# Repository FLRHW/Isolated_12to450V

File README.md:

<p align="center" width="100%">
  
</p>

***

<p align="center">
  
&nbsp; &nbsp; &nbsp; &nbsp;
  
</p>

***

# **Isolated step-up module**
This repository contains KiCad schematic and PCB layout of a step-up module prototype, isolated, capable of producing outputs in the range of 160 V to 450 V from a 12 V supply.

## Project overview
This project documents the conversion of a commercial non-isolated step-up module originally purchased from AliExpress into isolated.

## Origin and scope
Original hardware: generic module purchased from AliExpress (exact vendor and listing may change over time, the following terms can help finding similar modules: "70W DC-DC 12V 24V To 200V-450V Voltage Adjustable Boost Power Converter Nixie Clock Tube Amplifier Capacitor Charging").  

Redesigned hardware: new schematic and PCB layout, but several parts from the original module have been reused (controller, transformer, connector, fuse and its holder, power MOSFET, output diode, trim-pot, power resistors and electrolytic capacitors). 

Status: prototype, partially tested. Not affiliated with, endorsed by, or supported by the original manufacturer or seller.

Contents: KiCad design files and supporting documentation.

## Intended use
This repository is intended for:
* Educational use and study of the circuit
* Repair, modification, or replacement of compatible hardware
* Integration into hobby or research projects, subject to any third‑party IP that may apply in your jurisdiction. Users are responsible for checking any patent, copyright, or regulatory constraints that may apply to their own use

## License
The KiCad design files and documentation in this repository are released under the CERN Open Hardware Licence v2 – Permissive (CERN‑OHL‑P‑2.0). SPDX identifier: CERN-OHL-P-2.0 See the LICENSE file for the full legal text and conditions.  

In short and non‑legal terms, you are free to use, modify, manufacture, and distribute hardware based on these files, provided you respect attribution requirements and the terms in the license.

## Trademarks and third‑party rights
All product names, logos, and brands of the original module are the property of their respective owners and are not included or licensed here.  

Any reference to third‑party marks is purely descriptive and does not imply endorsement or affiliation.  

If you are the rights holder for the original hardware and have concerns about this documentation, please open an issue in the repository.

## Safety and disclaimer
* The author takes no responsibility for any injury, death or damage arising from the use, direct or indirect, of the design or otherwise any information from this repository
* You shall not build this or any prototype based on this design unless you are absolutely sure of your abilities dealing with this type of circuit
* High voltage can cause injury, death, or damage to equipment. Ensure appropriate protections and testing procedures are followed
* Use it at your own risk. Always review the schematic, layout, and component ratings before using it
* The design is provided as is, with no warranty of any kind

## Contributing
Contributions are welcome.

***

## DIRECTORY STRUCTURE
    │
    ├─ Computations       # Misc calculations
    ├─ HTML               # HTML files for generated webpage
    ├─ Images             # Pictures and renders
    │
    ├─ kibot_resources    # External resources for KiBot
    │  ├─ colors          # Color theme for KiCad
    │  ├─ fonts           # Fonts used in the project
    │  ├─ scripts         # External scripts used with KiBot
    │  └─ templates       # Templates for KiBot generated reports
    │
    ├─ kibot_yaml         # KiBot YAML config files
    ├─ KiRI               # KiRI (PCB diff viewer) files
    │
    ├─ lib                # KiCad footprint and symbol libraries
    │  ├─ 3d_models       # Component 3D models
    │  ├─ lib_fp          # Footprint libraries
    │  └─ lib_sym         # Symbol libraries
    │
    ├─ Logos              # Logos
    │
    ├─ Manufacturing      # Assembly and fabrication documents
    │  ├─ Assembly        # Assembly documents (BoM, pos, notes)
    │  │
    │  └─ Fabrication     # Fabrication documents (ZIP, notes)
    │     ├─ Drill Tables # CSV drill tables
    │     └─ Gerbers      # Gerbers
    │
    ├─ Reports            # Reports for ERC/DRC
    ├─ Schematic          # PDF of schematic
    ├─ Templates          # Title block templates
    └─ Testing
       └─ Testpoints      # Testpoints tables

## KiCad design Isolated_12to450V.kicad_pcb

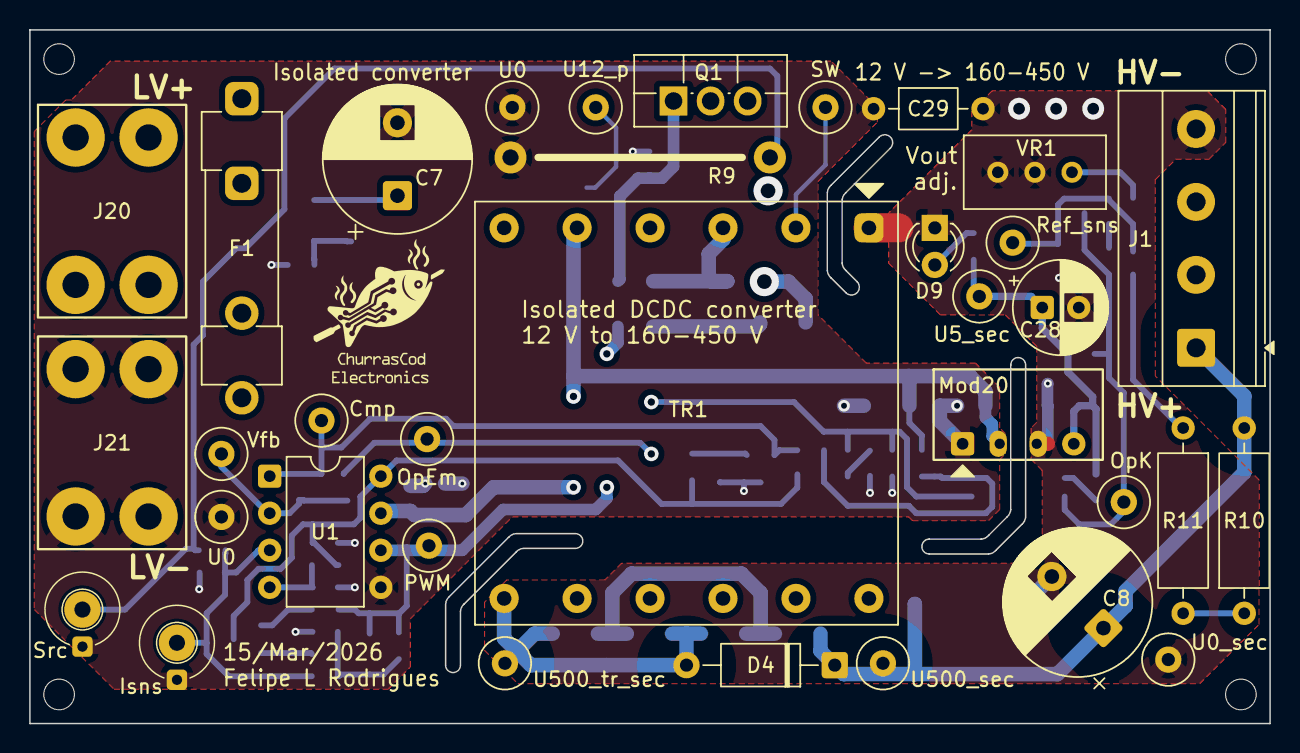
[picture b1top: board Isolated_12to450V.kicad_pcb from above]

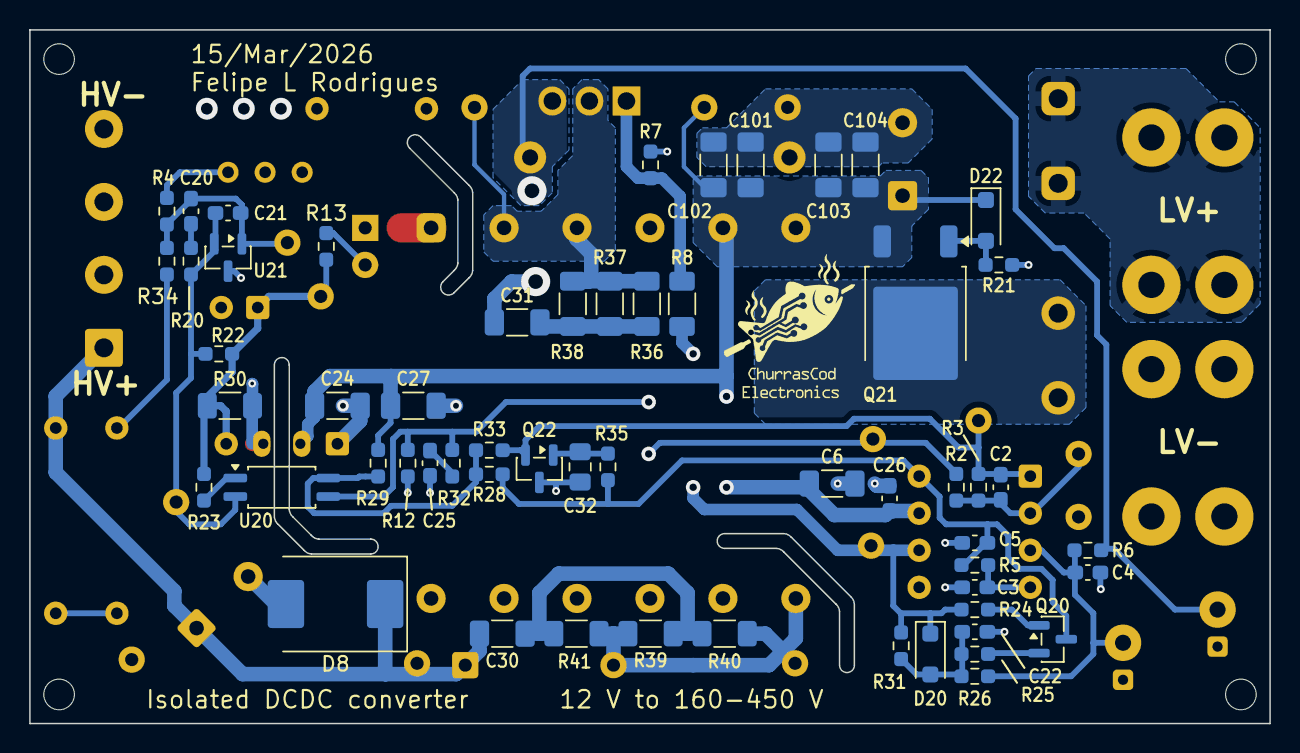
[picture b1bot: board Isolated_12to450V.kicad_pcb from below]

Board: 4 copper layers, 85.0 x 47.5 mm, 95 parts (57 on the bottom side), 35 nets.

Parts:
C2, C3, C4, C25: 1n; C_0603_1608Metric_Pad1.08x0.95mm_HandSolder
C5, C20, C26: 100n; C_0603_1608Metric_Pad1.08x0.95mm_HandSolder
C6, C24, C27, C101, C102, C103, C104: 4.7u; C_1206_3216Metric_Pad1.33x1.80mm_HandSolder
C7: 1000u; CP_Radial_D10.0mm_P5.00mm
C8: 10u; CP_Radial_D10.0mm_P5.00mm
C21: 100p; C_0603_1608Metric_Pad1.08x0.95mm_HandSolder
C22: 10n; C_0603_1608Metric_Pad1.08x0.95mm_HandSolder
C28: 100u; CP_Radial_D6.3mm_P2.50mm
C29: 1.5n; C_Axial_L3.8mm_D2.6mm_P7.50mm_Horizontal
C30: 220p; C_1206_3216Metric_Pad1.33x1.80mm_HandSolder
C31: 2.7n; C_1206_3216Metric_Pad1.33x1.80mm_HandSolder
C32: 1u; C_0805_2012Metric_Pad1.18x1.45mm_HandSolder
D4: UF4007; D_A-405_P10.16mm_Horizontal
D8: S15M; D_SMC
D9: LED; LED_D3.0mm
D20: PMEG4010CEH; D_SOD-123F
D22: BZT52B15; D_SOD-123F
F1: 10A; Fuse_5x20mm_w_holders
H1, H2, H3, H4: MountingHole; MountingHole_2.1mm
J1: Screw_Terminal_01x04; TerminalBlock_Phoenix_MKDS-1,5-4_1x04_P5.00mm_Horizontal
J20, J21: T44007
Mod20: WB2405S-1W; WB___S-1W
Q1: HY1707; TO-220F-3_Vertical
Q20: BC817; SOT-23
Q21: SUD50P06-15; TO-252-2
Q22: BC857; SOT-23
R2, R3, R21: 10k; R_0603_1608Metric_Pad0.98x0.95mm_HandSolder
R4: 2k7; R_0603_1608Metric_Pad0.98x0.95mm_HandSolder
R5: 15k; R_0603_1608Metric_Pad0.98x0.95mm_HandSolder
R6, R13, R29: 1k; R_0603_1608Metric_Pad0.98x0.95mm_HandSolder
R7: 5k1; R_0603_1608Metric_Pad0.98x0.95mm_HandSolder
R8: 20; R_1206_3216Metric_Pad1.30x1.75mm_HandSolder
R9: 13.7m; Shunt_alixp_module
R10, R11: 240k; R_Axial_DIN0309_L9.0mm_D3.2mm_P12.70mm_Horizontal
R12: 1k2; R_0603_1608Metric_Pad0.98x0.95mm_HandSolder
R20, R35: 100k; R_0603_1608Metric_Pad0.98x0.95mm_HandSolder
R22, R25, R31: 2k2; R_0603_1608Metric_Pad0.98x0.95mm_HandSolder
R23: 470; R_0603_1608Metric_Pad0.98x0.95mm_HandSolder
R24: 4k7; R_0603_1608Metric_Pad0.98x0.95mm_HandSolder
R26: 4.7k; R_0603_1608Metric_Pad0.98x0.95mm_HandSolder
R28, R32, R33, R34: 0; R_0603_1608Metric_Pad0.98x0.95mm_HandSolder
R30, R39, R40, R41: 470; R_1206_3216Metric_Pad1.30x1.75mm_HandSolder
R36, R37, R38: 33; R_1206_3216Metric_Pad1.30x1.75mm_HandSolder
TP9, TP10, TP20, TP23, TP24, TP25, TP26, TP27, TP28, TP30, TP31, TP32, TP33, TP34: TestPoint_Alt; TestPoint_Loop_D3.50mm_Drill0.9mm_Beaded
TP35, TP36: Testpoint_osc_no_lead
TR1: Custom_1:19.5; Tr12to450V_Alixp
U1: UC3845; DIP-8_W7.62mm
U20: TCMT1108; SOP-4_4.4x2.6mm_P1.27mm
U21: TL431M; SOT-23
VR1: 5k; Potentiometer_Bourns_3296W_Vertical

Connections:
/Block Diagram/Schematic/B: Q20.1 (B), R24.2
/Block Diagram/Schematic/Comp: C2.2, Q22.2 (E), R3.2, R33.2, TP25.1, U1.1 (COMP)
/Block Diagram/Schematic/E: Q20.2 (E), R25.2
/Block Diagram/Schematic/Gate: Q1.1 (G), R7.1, R8.2
/Block Diagram/Schematic/Isns: C4.1, R6.1, R26.2, TP35.1 (Sig), U1.3 (ISENSE)
/Block Diagram/Schematic/LED_A_sec: D9.2 (A), R13.2
/Block Diagram/Schematic/OpCol: R28.2, R29.2, R33.1, U20.4
/Block Diagram/Schematic/OpEm: R2.2, R12.1, R32.1, TP26.1, U20.3
/Block Diagram/Schematic/PWM: D20.1 (K), R8.1, R24.1, R31.2, TP23.1, U1.6 (OUTPUT)
/Block Diagram/Schematic/RP_Gate: D22.2 (A), Q21.1 (G), R21.1
/Block Diagram/Schematic/RT_CT: C3.1, R5.1, U1.4 (RT_CT)
/Block Diagram/Schematic/Ramp: C22.1, D20.2 (A), R25.1, R26.1, R31.1
/Block Diagram/Schematic/SW: Q1.2 (D), R36.1, R37.1, R38.1, TP20.1, TR1.2, TR1.3
/Block Diagram/Schematic/Sec_OpA: R23.1, U20.1
/Block Diagram/Schematic/Sec_OpK: C21.2, R20.1, R22.2, TP10.1, U20.2, U21.2 (K)
/Block Diagram/Schematic/Sec_cp_m: C20.2, R20.2
/Block Diagram/Schematic/Sec_div_h: R10.1, R11.2
/Block Diagram/Schematic/Sec_div_l: R4.2, VR1.3
/Block Diagram/Schematic/Sec_div_m: R11.1, R34.1
/Block Diagram/Schematic/Sec_ref_sns: C20.1, C21.1, R4.1, R34.2, TP9.1, U21.1 (REF)
/Block Diagram/Schematic/Src: C31.1, Q1.3 (S), R6.2, R9.1, TP36.1 (Sig)
/Block Diagram/Schematic/U5_ref: C5.1, Q20.3 (C), R5.2, R28.1, R35.1, U1.8 (VREF)
/Block Diagram/Schematic/U5_sec: C28.1, Mod20.4 (Vo+), R13.1, R22.1, R23.2, R30.1, TP34.1
/Block Diagram/Schematic/U12_f: F1.2, Q21.2 (D)
/Block Diagram/Schematic/U12_in: F1.1, J20.1
/Block Diagram/Schematic/U12_p: C6.1, C7.1, C24.1, C26.1, C27.1, C101.1, C102.1, C103.1, C104.1, D22.1 (K), Mod20.2 (Vin+), Q21.3 (S), R29.1, TP31.1, TR1.5, TR1.6, U1.7 (VCC)
/Block Diagram/Schematic/U500_sec: C8.1, C30.2, D4.1 (K), D8.1 (K), J1.1, R10.2, TP27.1
/Block Diagram/Schematic/U500_sn_sec: C30.1, R39.1, R40.1, R41.1
/Block Diagram/Schematic/U500_tr_sec: D4.2 (A), R39.2, R40.2, R41.2, TP30.1, TR1.7
/Block Diagram/Schematic/Vfb: C2.1, R2.1, R3.1, TP24.1, U1.2 (VFB)
unnamed: C25.1, R32.2
unnamed: C31.2, R36.2, R37.2, R38.2
unnamed: C32.1, Q22.1 (B), R35.2
U0: C3.2, C4.2, C5.2, C6.2, C7.2, C22.2, C24.2, C25.2, C26.2, C27.2, C29.1, C32.2, C101.2, C102.2, C103.2, C104.2, J21.1, Mod20.1 (Vin-), Q22.3 (C), R7.2, R9.2, R12.2, R21.2, TP32.1, TP33.1, TP35.2 (Ref), TP36.2 (Ref), U1.5 (GND)
U0_sec: C8.2, C28.2, C29.2, D8.2 (A), D9.1 (K), J1.4, Mod20.3 (0V), R30.2, TP28.1, TR1.1, U21.3 (A), VR1.1, VR1.2

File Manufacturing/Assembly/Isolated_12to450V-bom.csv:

Row,Quantity Per PCB,References,Value,Datasheet,Footprint,Description,Manufacturer,Manufacturer Part Number,Supplier Part Number
1,1,C21,100p,~,C_0603_1608Metric_Pad1.08x0.95mm_HandSolder,Unpolarized capacitor,,,
2,1,C30,220p,~,C_1206_3216Metric_Pad1.33x1.80mm_HandSolder,Unpolarized capacitor,,,
3,2,C3 C4,1n,~,C_0603_1608Metric_Pad1.08x0.95mm_HandSolder,Unpolarized capacitor,,,
4,1,C29,1.5n,~,C_Axial_L3.8mm_D2.6mm_P7.50mm_Horizontal,Unpolarized capacitor,,,
5,1,C31,2.7n,~,C_1206_3216Metric_Pad1.33x1.80mm_HandSolder,Unpolarized capacitor,,,
6,1,C22,10n,~,C_0603_1608Metric_Pad1.08x0.95mm_HandSolder,Unpolarized capacitor,,,
7,3,C5 C20 C26,100n,~,C_0603_1608Metric_Pad1.08x0.95mm_HandSolder,Unpolarized capacitor,,,
8,1,C32,1u,~,C_0805_2012Metric_Pad1.18x1.45mm_HandSolder,Unpolarized capacitor,,,
9,7,C6 C24 C27 C101 C102 C103 C104,4.7u,~,C_1206_3216Metric_Pad1.33x1.80mm_HandSolder,Unpolarized capacitor,,,
10,1,C8,10u,~,CP_Radial_D10.0mm_P5.00mm,Polarized capacitor,,,
11,1,C28,100u,~,CP_Radial_D6.3mm_P2.50mm,Polarized capacitor,,,
12,1,C7,1000u,~,CP_Radial_D10.0mm_P5.00mm,Polarized capacitor,,,
13,1,D22,BZT52B15,https://diotec.com/tl_files/diotec/files/pdf/datasheets/bzt5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,D_SOD-123F,"500mW Zener Diode, SOD-123F",,,
14,1,D9,LED,~,LED_D3.0mm,Light emitting diode,,,
15,1,D20,PMEG4010CEH,https://assets.nexperia.com/documents/data-sheet/PMEG4010CEH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,D_SOD-123F,"40V, 1A very low Vf MEGA Schottky barrier rectifier, SOD-123F",,,
16,1,D4,UF4007,~,D_A-405_P10.16mm_Horizontal,Diode,,,
17,1,F1,10A,~,Fuse_5x20mm_w_holders,Fuse,,,
18,1,J1,Screw_Terminal_01x04,~,"TerminalBlock_Phoenix_MKDS-1,5-4_1x04_P5.00mm_Horizontal","Generic screw terminal, single row, 01x04, script generated (kicad-library-utils/schlib/autogen/connector/)",,Generic screw terminal,
19,2,J20 J21,T44007,~,T44007,"Generic screw terminal, single row, 01x01, script generated (kicad-library-utils/schlib/autogen/connector/)",,T44007,
20,1,Mod20,WB2405S-1W,,WB___S-1W,,RLT,WB2405S-1W,
21,1,Q20,BC817,https://www.onsemi.com/pub/Collateral/BC818-D.pdf,SOT-23,"0.8A Ic, 45V Vce, NPN Transistor, SOT-23",,,
22,1,Q22,BC857,https://www.onsemi.com/pub/Collateral/BC860-D.pdf,SOT-23,"0.1A Ic, 45V Vce, PNP Transistor, SOT-23",,,
23,1,Q1,HY1707,~,TO-220F-3_Vertical,"N-MOSFET transistor, gate/drain/source",,,
24,1,Q21,SUD50P06-15,https://www.vishay.com/docs/68940/sud50p06.pdf,TO-252-2,"-50A Id, -60V Vds, TrenchFET P-Channel Power MOSFET, 15mOhm Ron, 165nC Qg, -55 to 150 °C, TO-252-2",,,
25,2,R28 R34,0,~,R_0603_1608Metric_Pad0.98x0.95mm_HandSolder,Resistor,,,
26,1,R9,13.7m,~,Shunt_alixp_module,Resistor,,,
27,1,R8,20,~,R_1206_3216Metric_Pad1.30x1.75mm_HandSolder,Resistor,,,
28,3,R36 R37 R38,33,~,R_1206_3216Metric_Pad1.30x1.75mm_HandSolder,Resistor,,,
29,1,R23,470,~,R_0603_1608Metric_Pad0.98x0.95mm_HandSolder,Resistor,,RC0603FR-07470RL,
30,4,R30 R39 R40 R41,470,~,R_1206_3216Metric_Pad1.30x1.75mm_HandSolder,Resistor,,RC1206JR-07470RL,
31,2,R6 R13,1k,~,R_0603_1608Metric_Pad0.98x0.95mm_HandSolder,Resistor,,,
32,1,R12,1k2,~,R_0603_1608Metric_Pad0.98x0.95mm_HandSolder,Resistor,,,
33,2,R22 R25,2k2,~,R_0603_1608Metric_Pad0.98x0.95mm_HandSolder,Resistor,,,
34,1,R4,2k7,~,R_0603_1608Metric_Pad0.98x0.95mm_HandSolder,Resistor,,,
35,2,R24 R26,4k7,~,R_0603_1608Metric_Pad0.98x0.95mm_HandSolder,Resistor,,,
36,1,R7,5k1,~,R_0603_1608Metric_Pad0.98x0.95mm_HandSolder,Resistor,,,
37,3,R2 R3 R21,10k,~,R_0603_1608Metric_Pad0.98x0.95mm_HandSolder,Resistor,,,
38,1,R5,15k,~,R_0603_1608Metric_Pad0.98x0.95mm_HandSolder,Resistor,,,
39,2,R20 R35,100k,~,R_0603_1608Metric_Pad0.98x0.95mm_HandSolder,Resistor,,,
40,2,R10 R11,240k,~,R_Axial_DIN0309_L9.0mm_D3.2mm_P12.70mm_Horizontal,Resistor,,,
41,1,TR1,Custom_1:19.5,,Tr12to450V_Alixp,,,,
42,1,U20,TCMT1108,http://www.vishay.com/docs/83510/tcmt1100.pdf,SOP-4_4.4x2.6mm_P1.27mm,"Optocoupler, Vce 70V, CTR 130-260%, Viso 3750V (RMS), SOP-4",,TCMT1108,
43,1,U21,TL431M,,SOT-23,"Shunt Regulator, SOT-23",FOSAN,TL431M-0.3%-6AF,
44,1,U1,UC3845,,DIP-8_W7.62mm,,,,
45,1,VR1,5k,~,Potentiometer_Bourns_3296W_Vertical,Trim-potentiometer,,,

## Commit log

2025-12-30 Initial commit, no junk
2025-12-30 Update Outputs
2026-01-03 Sch and PCB ready, using existing PCB as basis w aux PCB for new parts
2026-01-03 Updated state and changelog, fixed DRC issues
2026-01-03 changed to checked
2026-01-03 Updated ci file to trigger workflow on any dev* branch
2026-01-04 Minor schematic changes (arrangement only)
2026-01-04 Highlighted parts to be replaced on existing module
2026-01-24 First working prototype - still not isolated
2026-01-24 First working prototype - still not isolated, ERC and DRC clear
2026-01-24 Update CHANGELOG
2026-01-24 Update Outputs (release)
2026-01-26 Schematic topology completed, adjusting packages
2026-01-27 Several footprint updates
2026-01-28 Layout started
2026-01-28 Layout candidate drafted
2026-01-28 Layout candidate #2 (draft)
2026-01-30 Layout in progress, added some rules and net classes
2026-01-31 All rules added, ready to start routing
2026-02-01 Routing complete
2026-02-01 Libraries added, revision notes and readme updated
2026-02-02 Added other design into PCB to take advantage of 100 x 100 mm limit from JLCPCB
2026-02-03 Investigating CI failure, no design changes
2026-02-04 Layout rework in progress after checking paper mock up
2026-02-05 Layout ready and checked
2026-02-06 Minor changes to resolve potential DFM issues flagged by JLCPCB
2026-02-06 Updated paths on footprint libraries to render 3D models on KiBot
2026-02-06 Removed extra prototyping area and started updating mfg docs
2026-02-06 Fixing issue in pdf fab yaml
2026-02-06 fixing templates
2026-02-06 resolving ci failure
2026-02-06 de-embedding pcb sheet template
2026-02-07 changed grid origin pos.
2026-02-07 Updated fab layers
2026-02-07 Tweaking yaml for mfg files
2026-02-07 Changed status to CHECKED, minor tweaks to mfg layers
2026-02-07 Updated main.yaml
2026-02-07 Preparing release
2026-02-07 Rev hist comments updated
2026-02-07 Revise README for isolated step-up module details
    Updated README to reflect changes in module description and project scope.
2026-02-07 Updated libraries and readme
2026-02-07 Revise README for isolated step-up module details
    Updated README to reflect changes in module description and status.
2026-02-07 Update README for clarity and formatting
2026-03-10 Sch update ongoing
2026-03-10 Further sch changes
2026-03-12 Schematic nearly complete
2026-03-13 added perfboard
2026-03-14 layout update started
2026-03-14 ERC/DRC completed
2026-03-14 Revised README
2026-03-14 Updating mfg drw
2026-03-15 Updated rev history
2026-03-15 another attempt to update rev hist
2026-03-15 Fix README from main
2026-03-15 updated libs and mfg docs
2026-03-15 update mfg docs and readme
2026-03-15 trying to fix readme
2026-03-15 testing readme fix
2026-03-15 Extra layers to fab doc
2026-03-15 Testing mirror text on fab doc
2026-03-15 Updated changelog
2026-03-15 Ready to release
2026-03-31 Trying linux setup
2026-03-31 Removed perfboard, new branch on linux
2026-03-31 Allowing workflow
2026-03-31 trying no verbose on log output
2026-03-31 trying to disable kiri
2026-03-31 KiRi to gitignore
2026-03-31 Added power on LED
2026-03-31 added logo
2026-03-31 updated supporting spreadsheet
2026-03-31 fixing pre set variables
